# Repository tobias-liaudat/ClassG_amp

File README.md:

# Diseño: Amplificador de Audio de Potencia Clase G con dos fuentes conmutadas

---

### Aspectos generales del trabajo

Este trabajo comprende el diseño, la simulación, la construcción y la medición de un amplificador de potencia de audio clase G más dos fuentes de switching.

El informe consiste en este repositorio en donde se pueden encontrar: distintos tipo de explicaciones del diseño; modelos de simulación; simulaciones de las características del amplificador diseñado; archivos del diseño de los distintos PCB y explicaciones conceptuales de las elecciones; mediciones de las características de los circuitos implementados.

Para navegar en este informe solo se debe seguir los distintos enlaces que irán abriendo las distintas carpetas. El informe consiste en dos carpetas principales, una que corresponde al [amplificador](https://github.com/tobias-liaudat/ClassG_amp/tree/master/Amplificador) y otra que corresponde a las [fuentes conmutadas](https://github.com/tobias-liaudat/ClassG_amp/tree/master/Fuente%20SW).

### Especificaciones

Las especificaiones del amplificador son las siguientes:

- Potencia: 40 W RMS @ 8 Ohm

- THD: < 0.1% @ 20Hz-20kHz, 5W / 8 Ohm

- THD: < 0.01% @ 1kHz, 15W / 8 Ohm

- IMD: < 0.05 % @ 60Hz & 7kHz, 4:1 razón de amplitudes

- Ancho de banda: 20Hz a 100kHz @ 0.1W / 8 Ohm

- Tensión continua a la salida: < |10mV|

- Sensibilidad: 1 Vp

- Impedancia de entrada: >10 kOhm

- Factor de Amortiguamiento: > 500

- Slew Rate: > 15 V/us

- Protección: contra cortocircuito y sobrecarga

---

### Algunos enlaces a distintas secciones del informe 

- [Mediciones del amplificador](https://github.com/tobias-liaudat/ClassG_amp/tree/master/Amplificador/Mediciones)

- [Diseño y simulaciones de características del amplificador](https://github.com/tobias-liaudat/ClassG_amp/tree/master/Amplificador/Dise%C3%B1o%20final)

- [Construcción y ruteo del amplificador](https://github.com/tobias-liaudat/ClassG_amp/tree/master/Amplificador/construccion)

- [Fuente de switching positiva: Topología Buck](https://github.com/tobias-liaudat/ClassG_amp/tree/master/Fuente%20SW/fuente_positiva)

### Videos de funcionamiento:

- Amplificador funcionando a máxima potencia y luego a baja potencia : [video](https://photos.app.goo.gl/b69a7zTJsys8Gchi9)

- Fuente de switching positiva trabajando con con carga de 16 Ohm : [video](https://photos.app.goo.gl/x3bsC1SKNY7uwe568)

- Fuente de switching negativa trabajando con con carga de 16 Ohm : [video](https://photos.app.goo.gl/3ddAb1sy1qB68Pso6)

- Amplificador con fuentes de switching trabajando a máxima potencia : [video](https://photos.app.goo.gl/AqDvbGj7fGZXpYhV9)

- Amplificador con fuentes de switching reproduciendo musica desde un celular en un parlante de 8 Ohm de baja potencia : [video](https://photos.app.goo.gl/HTU1mSpep7PGP6fW8)

---

## [Amplificador](https://github.com/tobias-liaudat/ClassG_amp/tree/master/Amplificador)

## [Fuentes Conmutadas](https://github.com/tobias-liaudat/ClassG_amp/tree/master/Fuente%20SW)

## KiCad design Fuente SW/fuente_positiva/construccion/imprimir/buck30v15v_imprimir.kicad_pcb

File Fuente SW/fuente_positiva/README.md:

# Buck converter

La topología elegida sirve para reducir tensiones, es decir que la tensión de salida sea menor a la de entrada. El esqumático del circuito elegido es el siguiente:

En este circuito se pueden identificar varias partes, los elementos principales de la fuente conmutada y elementos accesorios.

### Elementos esenciales

Para realizar la fuente, se debe elegir entre varios controladores por modulación de ancho de pulso para poder controlar las llaves y regular la tensión en un valor constante. En el mercado se encuentran varios modelos de controladores como el TL494 o el UC3843 que ya tienen trayectoria y son de bajo costo (~ USD 0.5). Sin embargo, no se encuentran modelos de SPICE oficiales para poder simular estos integrados, y además se deben complementar con un transistor de potencia que actúe como una de las llaves de la fuente de switching.

También existen otros integrados que incluyen a la llave de potencia como el LM2576-ADJ que puede ajustarse la realimentación para elegir la tensión de salida y esta diseñado para construir fuentes de switching reductoras como la topología buck. El precio no es tan elevado (~ USD 1.2) y puede manejar hasta 3A a la salida. El fabricante proporciona un modelo de SPICE del integrado que funciona bien, es decir con un tiempo de simulación acpetable. Por lo tanto, se decidió elegir al LM2576-ADJ como controlador. 

En este controlador la frecuencia de oscilación esta fijada en 52kHz y además incluye una protección que reduce la frecuencia a 11kHz cuando la corriente que se le pide al integrada es mucha y supera cierto valor. Esto es útil para limitar la corriente en el transitorio de encendido además de servir como una limitación contra un cortocircuito a la salida.

El modelo del diodo Schottky de conmutación se eligió teniendo en cuenta la simulación realizada para ver cuanta corriente debía soportar. Se sobredimensionó al elelgir el MUR820. El capacitor de entrada se eligió teniendo en cuenta la recomendación de la hoja de datos del LM2576-ADJ, y el capacitor de salida se ajusto según considerando el ripple a la salida y siguiendo lo detallado en la hoja de datos del controlador.

Los demas elementos de la fuente y su diseño se analizará a continuación.

### Elementos accesorios

En esta parte se encuentra un circuito de protección contra un baja tensión a la entrada. La tensión elegida fue de 18V que justamente es la tensión del diodo Zener 1N4746A presente en el circuito. Si la tensión es inferior a 18v el diodo Zener se encuentra en inversa y el transistor se despolariza, cambiando la tensión del pin ON/OFF del LM2576-ADJ apagandolo.

Luego, se incluyo un led indicador que se prende cuando la fuente esta encendida.

Finalmente, se incluyo una carga resistiva propia a la fuente para que no trabaje en vacio, y un fusible de protección a la salida. Este puede intercambiarse facilmente, son de bajo costo y se puede elegir el valor del fusible que se desee utilizar.

## Simulación

El circuito utilizado para la simulación es el siguiente y puede encontrarse en el siguiente [enlace](https://github.com/tobias-liaudat/ClassG_amp/tree/master/Fuente%20SW/fuente_positiva/simulacion).

El modo de operación elegido fue el discontinuo. La razón es que esta fuente se encontrara con la necesidad de estar sin entragar corriente por momentos, el caso en donde no hay señal a la entrada, ya que la polarización del amplificador proviene de los rieles superiores. Luego cuando el amplificador se encuentre funcionando, la fuente deberá entregar corriente solo en los momentos en que la señal de salida esté por debajo del valor de salida de la fuente, es decir 15V. Por lo tanto deberá entregar corriente por cortos periodos de tiempo para luego trabajar en vacio y repetir este ciclo. Se considero al modo discontinuo mejor adaptado para trabajar con una variación de carga de este tipo.

Este modo hace que el inductor requerido por la fuente sea menor, aunque va a exigir pico de corriente mayor.

En el siguiente grafico puede verse una simulación de la fuente operando primero en 'vacio' (con la carga interna de 330 Ohms) y luego con una carga de aproximadamente 2.4 A de media con una senoidal montada de 0.5A de amplitud. Se puede observar que no presenta ningún inconveniente para la fuente diseñada.

## Diseño del inductor

El inductor requerido debe ser de **30uH**. Se eligió este valor para que la fuente opere en modo discontinuo en todo el rango de operación. Para el diseño del inductor es importante realizar los cálculos para que este pueda soportar la corriente de la fuente sin saturarse. Para el diseño se siguieron los pasos especificados en el libro:

- *Sistemas de Alimentación Conmutados, de J. Luis Muñoz Sáez y S. Hernández González.*

Primero realizamos algunas especificaiones de la fuente que necesitamos para el diseño del inductor:

|        Parámetros de diseño        	|     Valor     	|
|:----------------------------------:	|:-------------:	|
|             Inductancia            	|      30uH     	|
|       Modo de funcionamiento       	|  Discontinuo  	|
|         Tensión de entrada         	|      +30V     	|
|          Tensión de salida         	|      +15V     	|
|                 Fs                 	|     52kHz     	|
|   Imp (corriente máxima pulsante)  	|      5.8A     	|
| Ie_max (corriente efectiva máxima) 	|      2.0A     	|
|             Delta_Temp             	| 40°C (típico) 	|
|             K = K_u K_p            	|  0.7 (típico) 	|
|               Delta_I              	|      5.8A     	|

Lo primero que hay que hacer es calcular el PA (Producto Area) que es justamente el producto del Ae (Area efectiva) y del Aw (Area de la ventana). Para esto existen dos fórmulas, que depende de si el tamaño del núcleo estará limitado por la saturación del mismo o por las pérdidas en el núcleo. Normalmente se utiliza la primera expresión si la operación es en modo continuo y a una frecuencia inferior a 500kHz, la segunda expresión se utiliza para el funcionamiento en modo discontinuo o caso de que la frecuencia de operación supere los 500kHz.

- Modo continuo:

- Modo discontinuo:

Una buena técnica de diseño consiste en calcular ambas expresiones y elegir el valor más grande. Al realizar el cálculo obtenemos:

- PA = 2376 mm4

Con este valor y conociendo la frecuencia de operación podemos hacer una elección provisora del núcleo en el fábricante de nucleos de ferrite que tengamos disponible. En nuestro caso, es el distribuidor [elemon](http://www.elemon.net/) que comercializa núcleos de distintos fabricantes.

Vamos a sobredimensionar el núcleo por protección. Primero se había seleccionado el núcleo E25/10/07 pero como no había stock se seleccionó el núcleo de ferrite **EER2811A** de material **CF196** del fabricante [Cosmo Ferrites](http://www.cosmoferrites.com/). En su página se encuentra las características del material como así las dimensiones del núcleo. 

A continuación se extrae del catálogo los extractos que describen al núcleo elegido:

### Material: CF196

### Forma: EER2811A

Del catálogo podemos extraer el valor de PA y también el valor de B_max del material.

- **PA = 8938 mm4**

- **B_max = 400mT @ 100°C**

Vamos a tomar un coeficiente de seguridad de 0.6 y establer que B_max_ef = 0.6 B_max = 240mT para los cálculos siguientes de número de espiras, largo del entrehierro y diametro del conductor.

#### Número de espiras

Para la determinación del número de espiras se utiliza la fórmula presente en la bibliografía mencionada que viene de una deducción de distintas ecuaciones.

Reemplazando con nuestros valores obtenemos:

- **N_min = 8.84 --> 9**

#### Longitud de entrehierro

Para la longitud del entrehierro se utiliza la formula siguiente donde *ur* es 1 ya que en el entrehierro habrá aire. *N* es el número de espiras que se calculó previamente.

Al reemplazar los valores obtenemos:

- **L_eh = 0.27mm**

#### Diametro del conductor

Utilizaremos las siguientes fórmulas donde reemplazaremos con nuestros valores. Luego de determinar el area de la sección del conductor realizamos una simple cuenta que vincula el área de una circunferencia con su diámetro.

El valor obtenido es:

- **D_c = 0.931 mm**

## Construcción del inductor

El alambre de cobre fue proporcionado por un amigo. Como este es de 0.7mm de diámetro y necesitamos de un diámetro mayor se decidió de trenzar el alambre para poder cumplir la condición planteada. Al ser una inductancia pequeña no es necesario muchas vueltas por lo que el espacio proporcionado por el nucleo alcanzará para poder construirlo.

Como comercialmente no se encuentra cualquier valor de entrehierro, se tomó una logitud de 0.5mm que se encontraba disponible por el fabricante.

### Núcleo de ferrite

### Carrete horizontal

### Yugo plástico

### Alambre de cobre esmaltado

### Inductor contruido

### Medición de la inductancia

## Diseño y Construcción del PCB

Para la diseño del PCB se siguieron los lineamientos dados en la materia. Como es una fuente que trabajará con potencia y además con una frecuencia alta, se debio utilizar zonas grandes para las distintas tensiones como *Vin*, *GND* y *Vout*. Se busca que las señales de alta frecuencia encuentren caminos de baja impedancia. 

Los archivos de diseño del programa *Kicad* se encuentran el esta [carpeta](https://github.com/tobias-liaudat/ClassG_amp/tree/master/Fuente%20SW/fuente_positiva/construccion).

### Vista atras

### Vista adelante

### Fuente construida

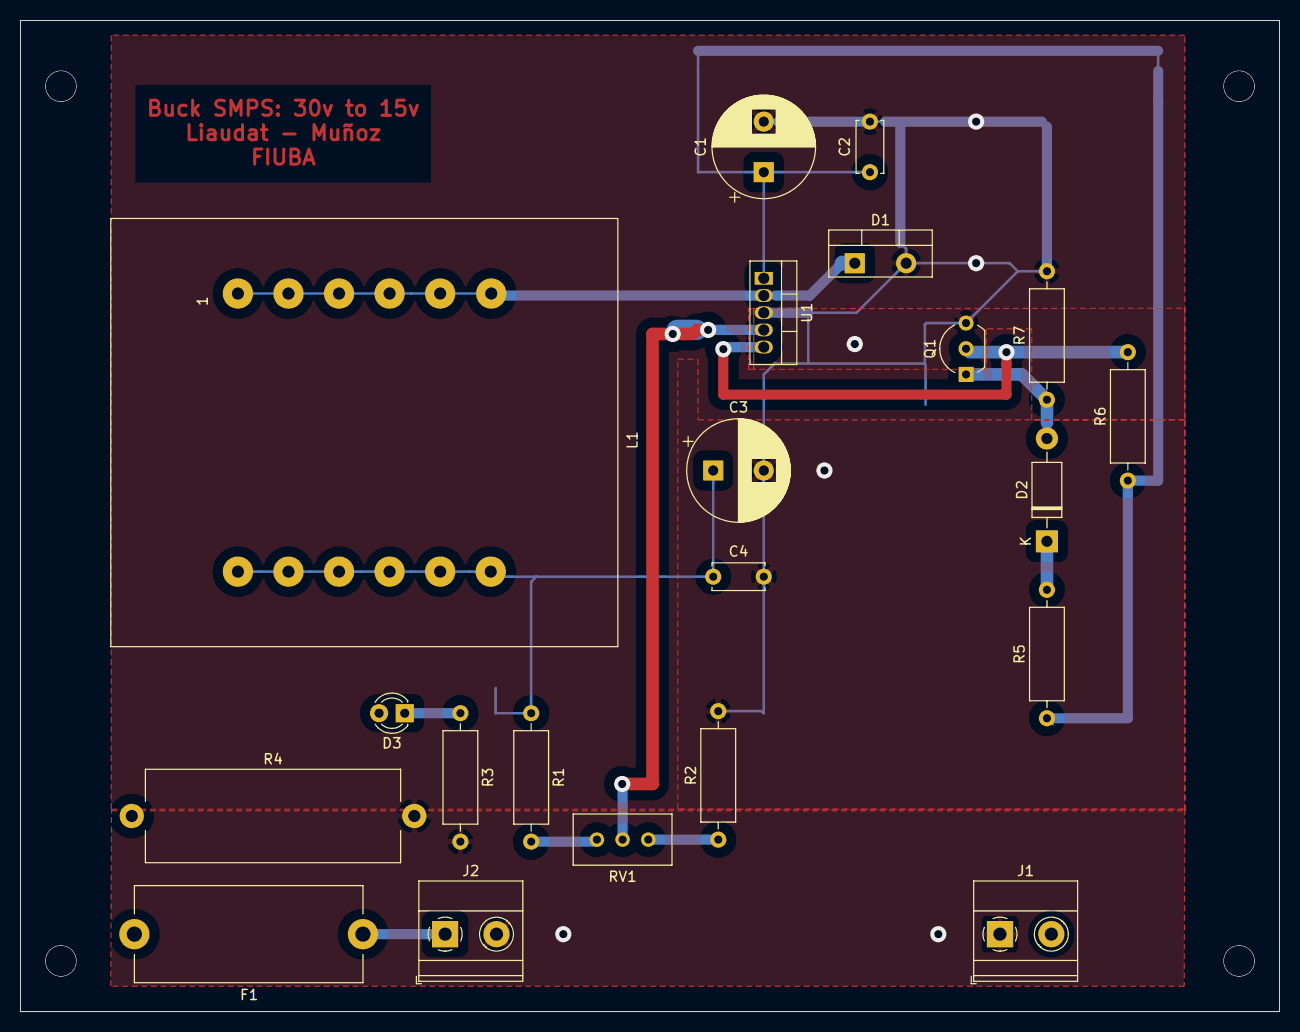
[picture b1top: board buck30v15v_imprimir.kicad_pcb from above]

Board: 2 copper layers, 124.5 x 98.0 mm, 21 parts (0 on the bottom side), 12 nets.

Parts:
C1, C3: 220u; CP_Radial_D10.0mm_P5.00mm
C2, C4: 100n; C_Disc_D5.0mm_W2.5mm_P5.00mm
D1: MUR820; TO-220-2_Vertical
D2: 1N4746A; D_DO-41_SOD81_P10.16mm_Horizontal
D3: LED; LED_D3.0mm
F1: 3A; Fuseholder_Cylinder-5x20mm_Stelvio-Kontek_PTF78_Horizontal_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
J1, J2: Conn_01x02; TerminalBlock_Phoenix_MKDS-1,5-2-5.08_1x02_P5.08mm_Horizont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
L1: 30uH; Transformer_CHK_EI48-8VA_Neutral
Q1: BC546B; TO-92_Inline_Wide
R1, R7: 10k; R_Axial_DIN0309_L9.0mm_D3.2mm_P12.70mm_Horizontal
R2, R3: 1k; R_Axial_DIN0309_L9.0mm_D3.2mm_P12.70mm_Horizontal
R4: 330; R_Axial_Power_L25.0mm_W9.0mm_P27.94mm
R5, R6: 20k; R_Axial_DIN0309_L9.0mm_D3.2mm_P12.70mm_Horizontal
RV1: 2k; Potentiometer_Bourns_3296W_Vertical
U1: LM2576T-ADJ; TO-220-5_Vertical

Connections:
GND: C1.2, C2.2, C3.2, C4.2, D1.2, J1.1, J2.2, Q1.3, R2.2, R3.2, R4.2, R7.2, U1.3
unnamed: C1.1, C2.1, J1.2, R5.1, R6.1, U1.1
unnamed: C3.1, C4.1, D3.2, F1.2, L1.7, L1.8, L1.9, L1.10, L1.11, L1.12, R1.1, R4.1
unnamed: D1.1, L1.1, L1.2, L1.3, L1.4, L1.5, L1.6, U1.2
unnamed: D2.1, R5.2
unnamed: D2.2, Q1.1, R7.1
unnamed: D3.1, R3.1
unnamed: F1.1, J2.1
unnamed: Q1.2, R6.2, U1.5
unnamed: R1.2, RV1.1
unnamed: R2.1, RV1.3
unnamed: RV1.2, U1.4

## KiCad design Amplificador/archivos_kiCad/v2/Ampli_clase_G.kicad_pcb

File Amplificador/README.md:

# Amplificadorde audio Clase G

Esta es la carpeta principal del diseño del amplificador de audio clase G de 40W. Vamos a hacer una pequeña descripción de las carpetas:

### Diseño y simulaciones

- [claseG_basico:](https://github.com/tobias-liaudat/ClassG_amp/tree/master/Amplificador/claseG_basico) es el circuito base del cual se comenzó el diseño.

- [claseG_mejoras:](https://github.com/tobias-liaudat/ClassG_amp/tree/master/Amplificador/claseG_mejoras) se listan varias de las mejoras propuestas al circuito.

- [modelo_componentes:](https://github.com/tobias-liaudat/ClassG_amp/tree/master/Amplificador/modelo_componentes) se incluyen los modelos de SPICE de los componentes utilizados.

- [potencia_rielesAlimentacion:](https://github.com/tobias-liaudat/ClassG_amp/tree/master/Amplificador/potencia_rielesAlimentacion) se encuentran unas simulaciones necesarias para determinar la elección de los rieles de alimentación y de la potencia requerida por las fuentes de switching.

- [claseG_componentes_reales:](https://github.com/tobias-liaudat/ClassG_amp/tree/master/Amplificador/claseG_componentes_reales) se incluye el circuito con la elección de componentes a utilizar y su respectiva lista.

- [Diseño final:](https://github.com/tobias-liaudat/ClassG_amp/tree/master/Amplificador/Dise%C3%B1o%20final) se incluye el circuito del diseo final con un vasto número de simulaciones y características del mismo.

- [Ajuste de ganancia y Disipadores:](https://github.com/tobias-liaudat/ClassG_amp/tree/master/Amplificador/Ajustes_ganancia_alimentacion) se incluyen modificaciones para que el circuito pueda trabajar en tres modos, con alimentación del riel superior de 30v, 40v o 50v. Además están los cálculos para la elección de los disipadores.

### Construcción

- [Construcción del circuito:](https://github.com/tobias-liaudat/ClassG_amp/tree/master/Amplificador/construccion) Esta carpeta incluye el diseño del circuito impreso con todos los archivos correspondiente del programa Kicad.

### Mediciones

- [Mediciones al amplificador:](https://github.com/tobias-liaudat/ClassG_amp/tree/master/Amplificador/Mediciones) En esta carpeta se pueden encontrar todas las distintas mediciones que se le realizaron al amplificador.

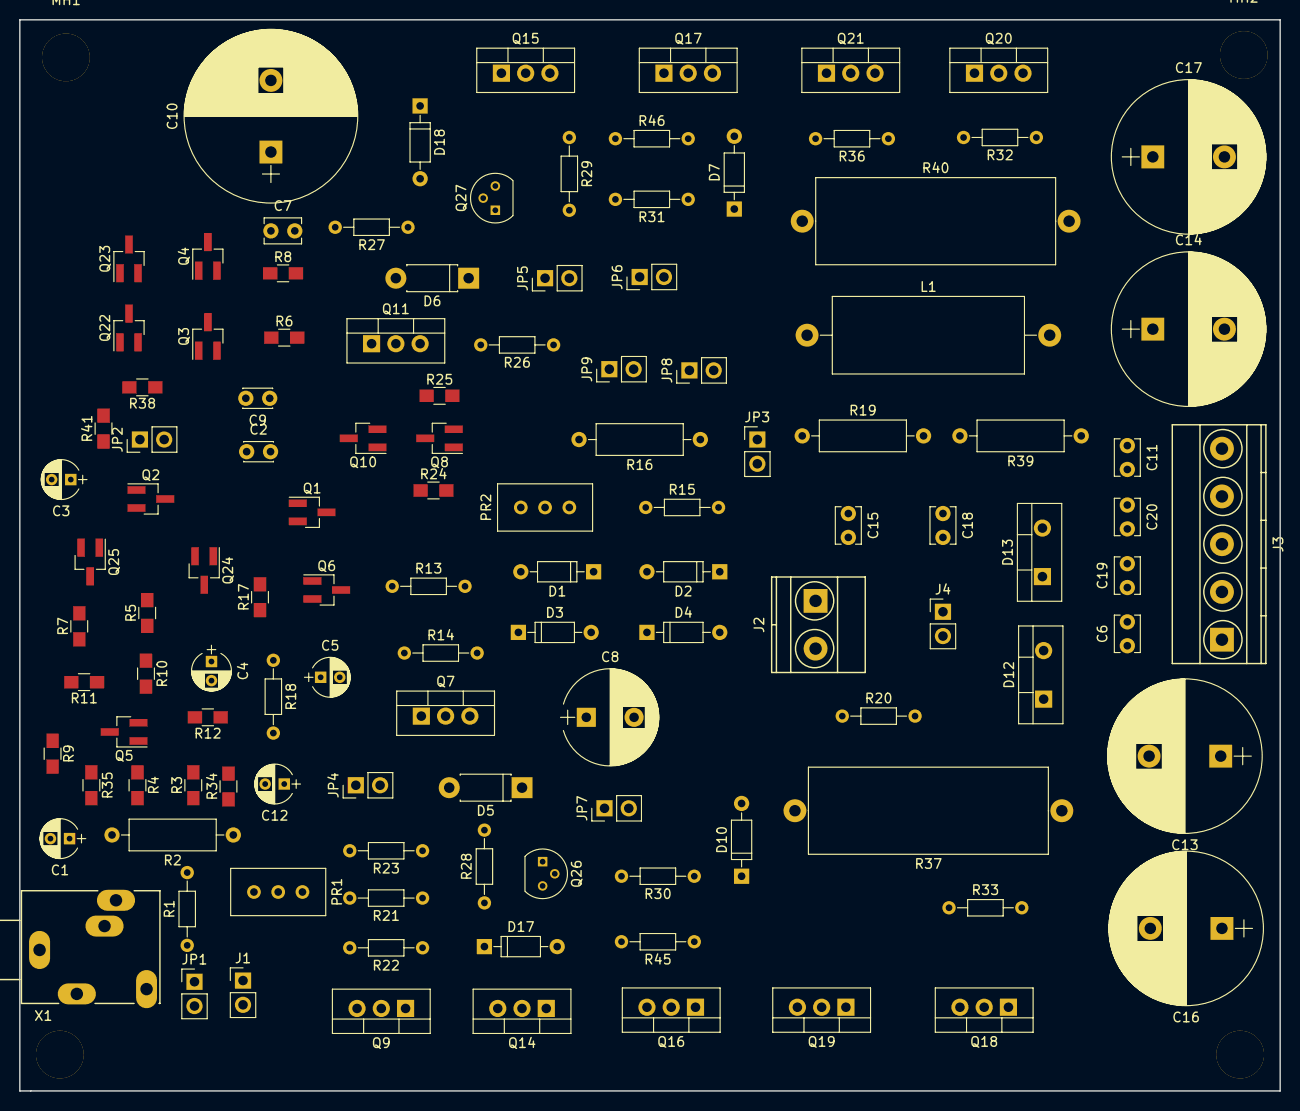
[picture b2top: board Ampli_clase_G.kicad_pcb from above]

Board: 2 copper layers, 132.0 x 112.1 mm, 121 parts (0 on the bottom side), 70 nets, no tracks yet.

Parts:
C1, C4, C5, C12: 47u; CP_Radial_D4.0mm_P2.00mm
C2: 0.3n; C_Disc_D3.0mm_W2.0mm_P2.50mm
C3: 100u; CP_Radial_D4.0mm_P2.00mm
C6, C7, C11, C15, C18, C19, C20: 100n; C_Disc_D3.8mm_W2.6mm_P2.50mm
C8: 1000u; CP_Radial_D10.0mm_P5.00mm
C9: 33p; C_Disc_D3.0mm_W2.0mm_P2.50mm
C10: 1000u; CP_Radial_D18.0mm_P7.50mm
C13, C14, C16, C17: 220u; CP_Radial_D16.0mm_P7.50mm
D1, D2, D3, D4, D7, D10, D17, D18: 1N4148; D_DO-35_SOD27_P7.62mm_Horizontal
D5, D6: 1N4728; D_DO-41_SOD81_P7.62mm_Horizontal
D12, D13: MUR860; TO-220-2_Vertical
J1: Conn_IN; Pin_Header_Straight_1x02_Pitch2.54mm
J2: LOAD_CONN; TerminalBlock_Phoenix_MKDS1.5-2pol
J3: SUPPLY_CONN; TerminalBlock_Phoenix_MKDS1.5-5pol
J4: CONN_OUT; Pin_Header_Straight_1x02_Pitch2.54mm
JP1: Jumper_NO_Small; Pin_Header_Straight_1x02_Pitch2.54mm
JP2: Diff_Stage_Jumper; Pin_Header_Straight_1x02_Pitch2.54mm
JP3: Jumper_Q2; Pin_Header_Straight_1x02_Pitch2.54mm
JP4: Low_Pos_Jumper; Pin_Header_Straight_1x02_Pitch2.54mm
JP5: Low_Neg_Jumper; Pin_Header_Straight_1x02_Pitch2.54mm
JP6: High_Neg_Jumper; Pin_Header_Straight_1x02_Pitch2.54mm
JP7: High_Pos_Jumper; Pin_Header_Straight_1x02_Pitch2.54mm
JP8: Jumper_Feedback; Pin_Header_Straight_1x02_Pitch2.54mm
JP9: Jumper_2ndStage; Pin_Header_Straight_1x02_Pitch2.54mm
L1: 1u; L_Axial_L20.0mm_D8.0mm_P25.40mm_Horizontal
MH1, MH2, MH3, MH4: MountingHole_5mm
PR1: 1k; Potentiometer_Trimmer_Suntan_TSR-3386C_Vertical
PR2: 100; Potentiometer_Trimmer_Suntan_TSR-3386C_Vertical
Q1, Q2, Q5, Q6: BC856; SOT-23_Handsoldering
Q3, Q4, Q8, Q10, Q22, Q23, Q24, Q25: BC846; SOT-23_Handsoldering
Q7, Q9, Q11, Q14, Q16: 2SC4793; TO-220-3_Vertical
Q15, Q17: 2SA1837; TO-220-3_Vertical
Q18, Q19: 2SC5200; TO-220-3_Vertical
Q20, Q21: 2SA1943; TO-220-3_Vertical
Q26: MPSA42; TO-92_Molded_Narrow
Q27: MPSA92; TO-92_Molded_Narrow
R1: 100k; R_Axial_DIN0204_L3.6mm_D1.6mm_P7.62mm_Horizontal
R2, R19, R39: 10; R_Axial_DIN0309_L9.0mm_D3.2mm_P12.70mm_Horizontal
R3, R4, R11, R12, R17, R24, R25, R34, R35, R38, R41: 2.2k; R_0805_HandSoldering
R5, R7, R9, R10: 100; R_0805_HandSoldering
R6, R8: 68; R_0805_HandSoldering
R13, R14: 10k; R_Axial_DIN0204_L3.6mm_D1.6mm_P7.62mm_Horizontal
R15: 51; R_Axial_DIN0204_L3.6mm_D1.6mm_P7.62mm_Horizontal
R16: 2.2k; R_Axial_DIN0309_L9.0mm_D3.2mm_P12.70mm_Horizontal
R18: 33; R_Axial_DIN0204_L3.6mm_D1.6mm_P7.62mm_Horizontal
R20, R28, R29, R32, R33, R36, R46: 100; R_Axial_DIN0204_L3.6mm_D1.6mm_P7.62mm_Horizontal
R21: 3.3k; R_Axial_DIN0204_L3.6mm_D1.6mm_P7.62mm_Horizontal
R22: 390; R_Axial_DIN0204_L3.6mm_D1.6mm_P7.62mm_Horizontal
R23: 16; R_Axial_DIN0204_L3.6mm_D1.6mm_P7.62mm_Horizontal
R26, R27: 10; R_Axial_DIN0204_L3.6mm_D1.6mm_P7.62mm_Horizontal
R30: 560; R_Axial_DIN0204_L3.6mm_D1.6mm_P7.62mm_Horizontal
R31: 180; R_Axial_DIN0204_L3.6mm_D1.6mm_P7.62mm_Horizontal
R37, R40: 0.22; R_Axial_Power_L25.0mm_W9.0mm_P27.94mm
R45: 330; R_Axial_DIN0204_L3.6mm_D1.6mm_P7.62mm_Horizontal
X1: Jack_IN; Stereo_Jack_3.5mm_Switch_Ledino_KB3SPRS

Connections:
+VCC_15V: C16.1, C19.1, D12.2, J3.2
+VCC_40V: C4.1, C5.1, C6.1, C13.1, J3.1, Q6.2, Q14.2, Q16.2, Q18.2, R10.1, R18.1
GND: C2.2, C6.2, C7.1, C8.2, C10.1, C11.2, C13.2, C14.1, C15.2, C16.2, C17.1, C19.2, C20.2, D2.1, D4.2, J1.2, J2.2, J3.3, J4.2, JP1.2, JP3.2, Q10.3, R1.2, R4.2, R14.2, R35.2, X1.2
unnamed: C1.1, R2.2
unnamed: C1.2, J1.1, JP1.1, R1.1, X1.1
unnamed: C2.1, Q1.1, R2.1, R3.1, R34.1
unnamed: C3.1, Q2.1, R15.2, R16.2
unnamed: C3.2, R9.1
unnamed: C4.2, Q5.1, R12.2
unnamed: C5.2, R13.2, R14.1
unnamed: C8.1, D1.2, D3.1, PR2.1
unnamed: C9.1, D6.2, JP6.1, JP9.1, Q11.2
unnamed: C9.2, JP2.2, Q8.3, Q10.1
unnamed: C7.2, C10.2, Q8.2, R6.2, R8.2, R25.2, R26.2, R27.2
unnamed: C12.1, JP4.1, Q9.2, R23.2
unnamed: C12.2, D6.1, JP5.1, PR1.2, PR1.3, Q9.3
unnamed: C15.1, R19.2
unnamed: C18.1, Q14.3, Q19.1, R20.1
unnamed: C18.2, Q15.3, Q20.1, R32.2
unnamed: D1.1, D2.2
unnamed: D3.2, D4.1
unnamed: D5.1, JP7.1, Q7.3
unnamed: D5.2, R21.1, R23.1
unnamed: D7.1, JP6.2
unnamed: D7.2, Q17.1
unnamed: D10.1, Q16.1
unnamed: D10.2, JP7.2
unnamed: D12.1, Q18.3, Q19.2, R33.1
unnamed: D13.2, Q20.2, Q21.3, R36.1
unnamed: D17.1, Q26.3
unnamed: D17.2, Q14.1, R28.1
unnamed: D18.1, Q15.1, R29.1
unnamed: D18.2, Q27.3
unnamed: J2.1, J4.1, L1.2, R39.1
unnamed: JP2.1, Q22.3, Q24.2, R38.2
unnamed: JP3.1, JP8.1, JP9.2, R16.1
unnamed: JP4.2, R28.2
unnamed: JP5.2, R29.2
unnamed: JP8.2, L1.1, Q26.1, Q27.1, R19.1, R30.2, R31.1, R37.2, R39.2, R40.1
unnamed: PR1.1, R22.2
unnamed: PR2.2, PR2.3, R15.1
unnamed: Q1.2, Q24.3, R5.2
unnamed: Q1.3, Q24.1, R38.1
unnamed: Q2.2, Q25.3, R7.2
unnamed: Q2.3, Q25.1, R41.1
unnamed: Q3.2, R6.1
unnamed: Q4.2, R8.1
unnamed: Q5.2, R10.2
unnamed: Q5.3, R11.1
unnamed: Q6.1, R17.2
unnamed: Q6.3, Q7.1, R12.1, R13.1
unnamed: Q7.2, R17.1, R18.2
unnamed: Q8.1, R24.2
unnamed: Q9.1, R21.2, R22.1
unnamed: Q10.2, Q11.1, R25.1
unnamed: Q11.3, R24.1, R26.1
unnamed: Q16.3, Q18.1, R33.2
unnamed: Q17.3, Q21.1, R36.2
unnamed: Q19.3, R37.1, R45.1
unnamed: Q20.3, R40.2, R46.2
unnamed: Q22.1, Q23.1, Q23.3, Q25.2, R41.2
unnamed: Q3.1, Q3.3, Q4.1, Q22.2
unnamed: Q4.3, Q23.2
unnamed: Q26.2, R30.1, R45.2
unnamed: Q27.2, R31.2, R46.1
unnamed: R3.2, R4.1, R9.2, R34.2, R35.1
unnamed: R5.1, R7.1, R11.2
unnamed: R20.2, R32.1
VEE_-15V: C17.2, C20.1, D13.1, J3.4
VEE_-40V: C11.1, C14.2, J3.5, Q15.2, Q17.2, Q21.2, R27.1

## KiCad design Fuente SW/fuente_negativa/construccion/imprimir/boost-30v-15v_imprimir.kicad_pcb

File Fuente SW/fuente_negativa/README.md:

# Boost converter

En este caso vamos a elevar la tensión desde -30V hasta -15V.

## Diseño del inductor

En este caso se siguió el mismo procedimiento que para la fuente positiva. Los valores calculados son los siguientes:

- **PA = 7353 mm4**

- **N_min = 27**

- **L_eh = 0.5mm**

- **D_c = 0.73mm**

## Construcción del inductor

Se utilizó el mismo núcleo, la misma forma y material que para la fuente positiva. La única diferencia reside en que para esta no se trenzo el alambre de cobre ya que no hace falta.

### Inductor construido

### Inductancia medida

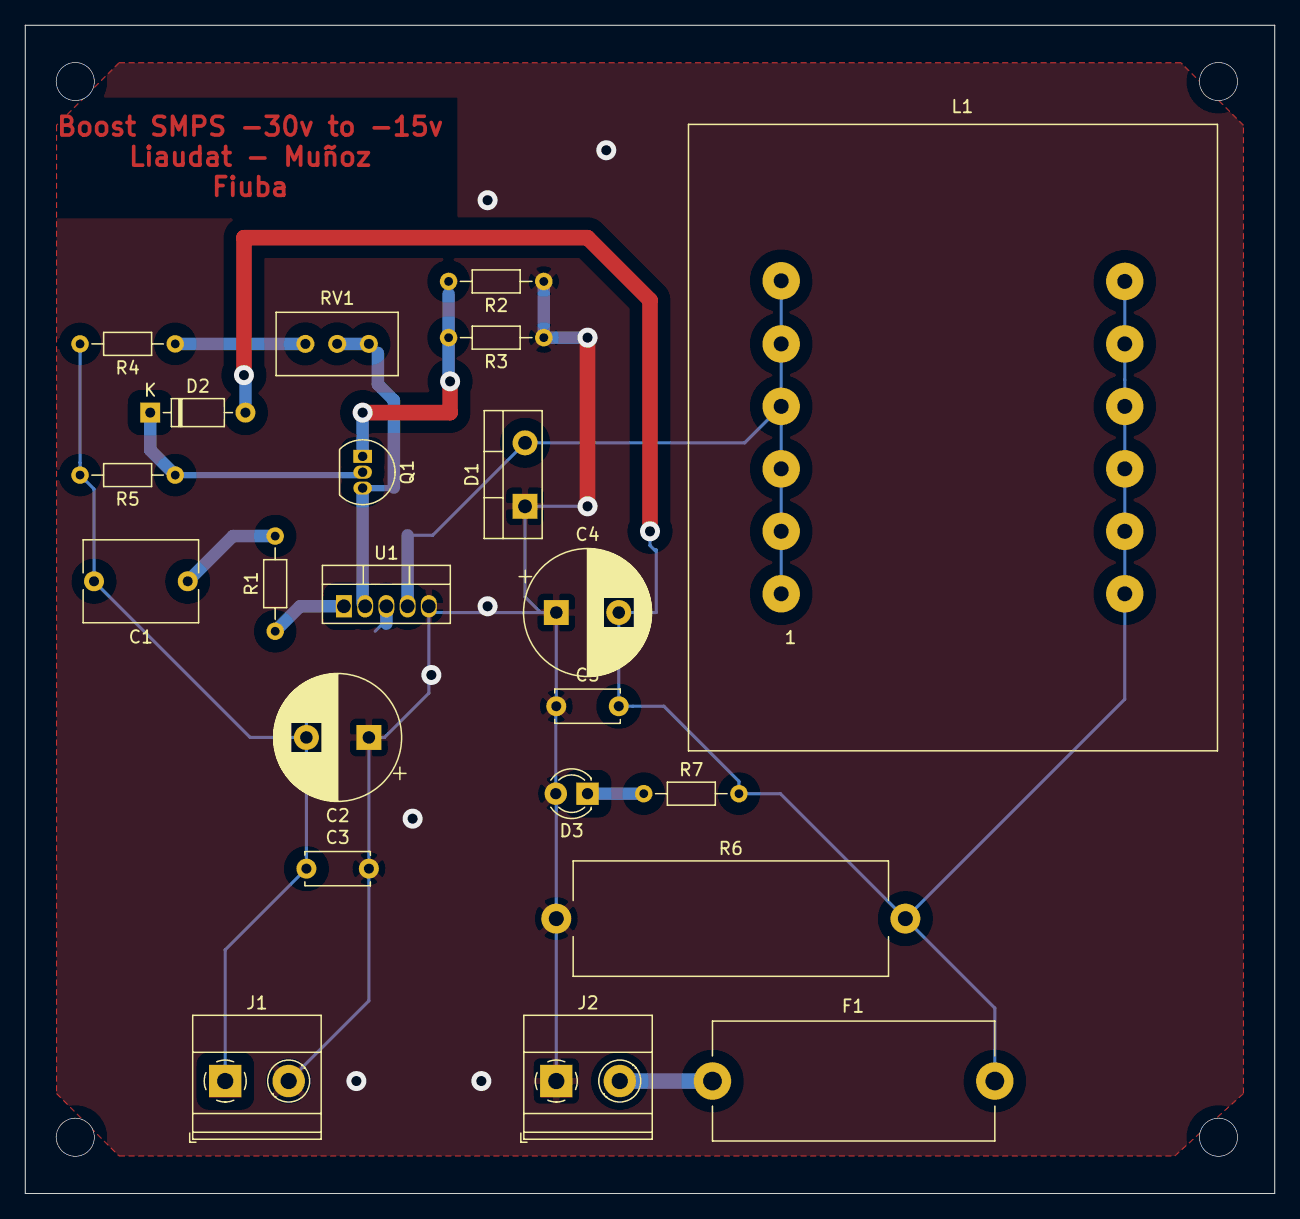
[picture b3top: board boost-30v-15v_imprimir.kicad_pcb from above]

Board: 2 copper layers, 100.0 x 93.5 mm, 22 parts (0 on the bottom side), 12 nets.

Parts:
C1: 0.22u; C_Rect_L9.0mm_W6.4mm_P7.50mm_MKT
C2: 220u; CP_Radial_D10.0mm_P5.00mm
C3, C5: 100n; C_Disc_D5.0mm_W2.5mm_P5.00mm
C4: 470u; CP_Radial_D10.0mm_P5.00mm
D1: MUR820; TO-220-2_Vertical
D2: 1N4148; D_DO-35_SOD27_P7.62mm_Horizontal
D3: LED; LED_D3.0mm
F1: Fuse 3A; Fuseholder_Cylinder-5x20mm_Stelvio-Kontek_PTF78_Horizontal_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
J1, J2: Conn_01x02; TerminalBlock_Phoenix_MKDS-1,5-2-5.08_1x02_P5.08mm_Horizont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
L1: 150uH; Transformer_CHK_EI48-8VA_Neutral
Q1: 2N3906; TO-92_Inline
R1: 3.3k; R_Axial_DIN0204_L3.6mm_D1.6mm_P7.62mm_Horizontal
R2, R3, R5: 100k; R_Axial_DIN0204_L3.6mm_D1.6mm_P7.62mm_Horizontal
R4: 3.9k; R_Axial_DIN0204_L3.6mm_D1.6mm_P7.62mm_Horizontal
R6: 330; R_Axial_Power_L25.0mm_W9.0mm_P27.94mm
R7: 1k; R_Axial_DIN0204_L3.6mm_D1.6mm_P7.62mm_Horizontal
RV1: 2k; Potentiometer_Bourns_3296W_Vertical
U1: LM2577; TO-220-5_Vertical

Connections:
GND: C2.1, C3.2, C4.1, C5.1, D1.1, D3.2, J1.2, J2.1, R2.1, R3.1, R6.1, U1.5
unnamed: C1.1, R1.2
unnamed: C1.2, C2.2, C3.1, J1.1, R4.2, R5.2, U1.3
unnamed: C4.2, C5.2, D2.2, F1.2, L1.7, L1.8, L1.9, L1.10, L1.11, L1.12, R6.2, R7.2
unnamed: D1.2, L1.1, L1.2, L1.3, L1.4, L1.5, L1.6, U1.4
unnamed: D2.1, Q1.2, R5.1
unnamed: D3.1, R7.1
unnamed: F1.1, J2.2
unnamed: Q1.1, R2.2, R3.2
unnamed: Q1.3, RV1.1, RV1.2, U1.2
unnamed: R1.1, U1.1
unnamed: R4.1, RV1.3

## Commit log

2019-05-29 Agrego los primeros modelos de spice
2019-05-29 Imagenes para el readme agregadas
2019-05-29 Agrego imagenes para el readme
2019-05-29 Nueva imagen para el readme
2019-05-29 cambio de nombre de una carpeta
2019-05-29 reestructuracion del arbol de carpetas
2019-05-29 agregado readme
2019-05-31 Update Readme
    Corregido mi nombre
2019-06-04 some folder changes. New current limit circuit
2019-06-04 new images added
2019-06-07 Nuevo circuito para medir potencia y ajustar los rieles de alimentacion
2019-06-09 modelos componentes reales añadidos. Nuevo limitador corriente y modelo con componentes reale
2019-06-09 Añadida lista de componentes
2019-06-09 new image
2019-06-09 Actualización del readme
2019-06-09 Cambios en Readme - Boost converter
2019-06-09 Spice Boost CCM vs DCM
2019-06-09 agrego Caracteristicas y simulaciones del diseño
2019-06-10 nuevas caracteristicas del diseño final
2019-06-10 nueva imagen
2019-06-10 nueva carpeta de polarizacion
2019-06-10 Simulaciones Boost en modo CCM
2019-06-10 Resultados de simulacion CCM
2019-06-10 Cambios en readme switching
2019-06-15 ultima version no funcional de la fuente boost
2019-06-15 nueva version de la boost
2019-06-22 nueva carpeta ajustes de ganancia y alimentacion
2019-06-23 imagenes añadidas
2019-06-23 nuevas imagenes y circuito calculo potencias
2019-06-23 Actualizados los componentes reales
2019-06-23 nuevo calculo de margen de fase
2019-06-23 reordenamiento de carpetas
2019-06-24 Archivos proyecto de Kicad - Amplificador
2019-06-24 Cambios en el esquematico de Kicad- Jumpers
2019-06-25 Archivos de Kicad Finales - Amplificador
2019-06-25 Push Kicad - Archivos faltantes
2019-06-25 Archivos de KiCad - Correccion de transistor Q7
2019-06-25 Captura Kicad
2019-06-25 imagenes viejas de SlewRate
2019-06-26 Gerbers Files - PCB Amp. terminada
2019-06-26 Gerbers - Archivos de proyecto
2019-06-28 Modificacion del footprint en los transistores de salida
    Modificación del footprint de TO220 a TO264. Agregado de los disipadores con sus puntos de atornillado a la placa.
2019-07-02 Version definitiva del amplificador
2019-07-20 kicad v14
2019-07-20 archivo que quedo colgado
2019-08-06 nuevas imagenes
2019-08-06 cosas
2019-08-06 nuevas mediciones
2019-08-06 polarizacion añadida
2019-08-08 Modificacion del esquematico
    Cambio de los transistores BC846 y BC856 por MMBTA42 y MMBTA92
2019-08-08 Modificacion readme
2019-08-08 modifs
2019-08-08 imagen eficiencia corregida
2019-08-08 nuevos graficos de mediciones
2019-08-08 nuevo grafico ancho de banda
2019-08-08 cambio imagen pot fuentes
2019-08-08 cambio grafico thd 1k
2019-08-08 graf thd 1k
2019-08-08 imagenes thd e imd
2019-08-09 nueva imagen generador
2019-08-09 rotar foto fuentes intro
2019-08-09 nueva estructura fuentes switching
2019-08-09 nueva imagen esquema
2019-08-09 cambio de lugar imagenes fuentes
2019-08-09 nuevas simulaciones fuente pos
2019-08-09 nuevas imagenes inductor pos
2019-08-09 archivos de construccion fuentes
2019-08-09 nueva imagen fuente pos
2019-08-12 simulacion gannacia lazo abierto
